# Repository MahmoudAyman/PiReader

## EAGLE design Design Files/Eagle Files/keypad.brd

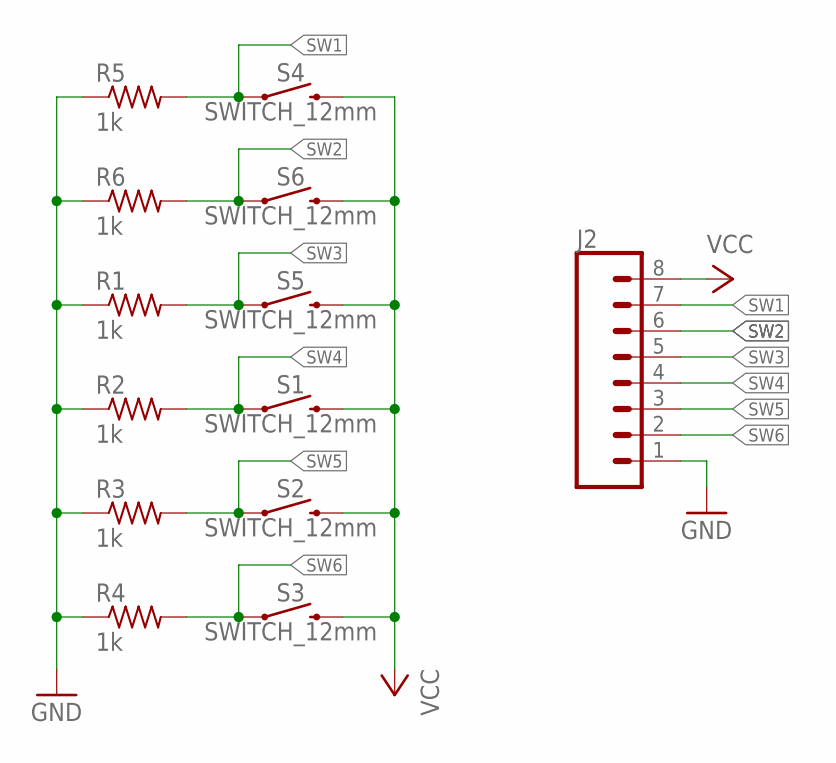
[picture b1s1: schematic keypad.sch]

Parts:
J2: CONN_08LONGPADS; 1X08_LONGPADS
R1, R2, R3, R4, R5, R6: 1k; 0207/10
S1, S2, S3, S4, S5, S6: SWITCH_12mm; TACTILE_SWITCH_PTH_12MM

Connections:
GND: J2.1, R1.1, R2.1, R3.1, R4.1, R5.1, R6.1
SW1: J2.7, R5.2, S4.1
SW2: J2.6, R6.2, S6.1
SW3: J2.5, R1.2, S5.1
SW4: J2.4, R2.2, S1.1
SW5: J2.3, R3.2, S2.1
SW6: J2.2, R4.2, S3.1
VCC: J2.8, S1.3 (2), S2.3 (2), S3.3 (2), S4.3 (2), S5.3 (2), S6.3 (2)

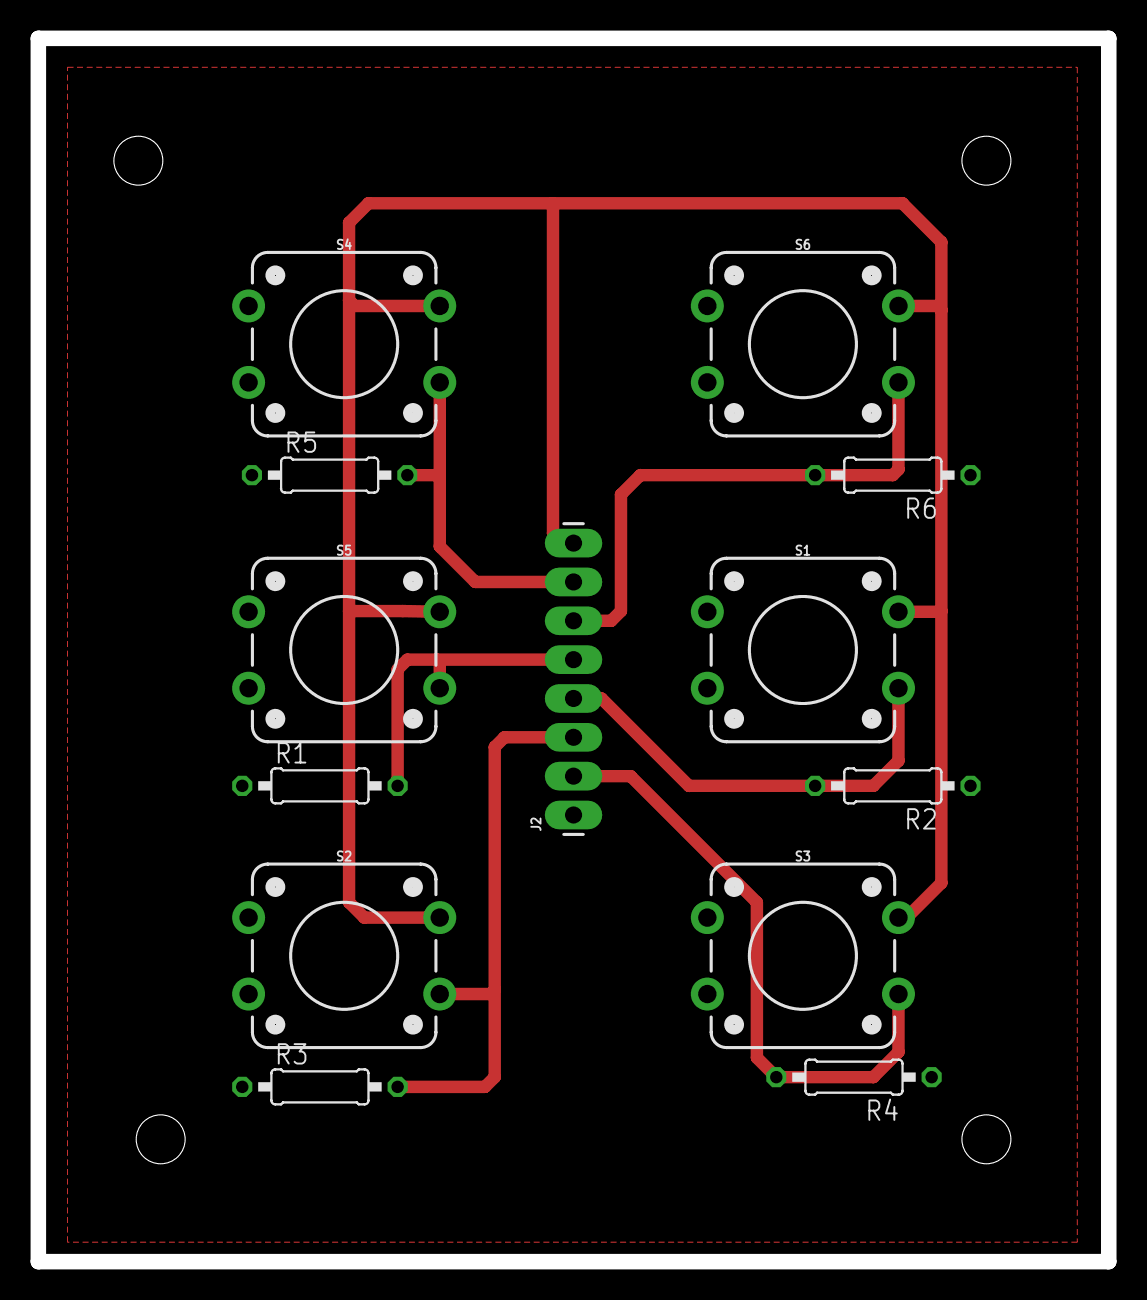
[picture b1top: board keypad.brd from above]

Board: 2 copper layers, 70.0 x 80.0 mm, 13 parts (0 on the bottom side), 8 nets.

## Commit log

2021-04-11 added the code for pre-alpha version
2021-04-11 Added requirements.txt
2021-04-11 added design files

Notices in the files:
parts and their libraries:
SparkFun-Switches: Licensing: Creative Commons ShareAlike 4.0 International - https://creativecommons.org/licenses/by-sa/4.0
microbuilder: This work is placed in the public domain, and may be freely used for commercial and non-commercial work with the following conditions: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
